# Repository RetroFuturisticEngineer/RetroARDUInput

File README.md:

# RetroARDUInput
Use USB Keyboards, Mice and Joysticks on PC/XT, PC/AT, Tandy 1000, Atari, Amiga, C64 and Apple

Requires Circuits@Home USB Host Shield 2.0 Library

Released before getting all components in a 100% working state, as I did not want to wait longer. Due to time limitations, I cannot guarantee to be finished soon with the last details, but by now, you can use all working components already. I will continue development but also encourage the retro computing community to help and contribute in fixing the last PS/2 and ADB issues.

You can find all required files here, the Arduino sketch (RetroArduInput_FW), the case, the PCB and a detailled documentation.

Current status of release:

Input:
- Working Input Devices:
  - Most normal USB Keyboards
  - Most normal USB Mice
  - Most USB Composite HIDs (Wireless USB Keyboard/Mouse)
  - USB Joysticks and Gamepads if they match to any of the implemented profiles
- Non-working or limited input devices (mostly limitations of the USB host shield library):
  - USB Hubs work random
  - No support for X-Box/Playstation USB gamepads
  - Problems with Gaming Keyboard/Mice with light effects etc.

Host Computers:
- Working computers to connect to:
  - PC/XT via Keyboard port
  - PC/AT via Keyboard port and PS/2 via adapter - includes typematic rate programming and LED set, however LEDs sometimes not properly set (only limitation)
  - Amiga 500 via Keyboard port when using an adapter to the internal keyboard port
  - Serial mouse with 2-button Microsoft and 3-button Logitech mode
  - Amiga/Atari mouse including switching of the X/Y pins between Atari and Amiga standard
  - Digital joystick, reacting to either joystick (normal joystick mode - uses a "dead zone" for analog joysticks to not immediately react on the slightest changes) and mouse (like a Commodore 1350 "Joymouse")
  - Analog joystick with 4 axis and 4 buttons
- Untested computers to connect to:
  - Tandy 1000 via keyboard port - adaptation of Adrian Black's PS/2 to Tandy, should work, but I cannot test it
  - Amiga 2000 via keyboard port - Should mostly work as mainly identical to Amiga 500, but uses a different routine during keyboard reset (Ctrl+Amiga+Amiga), which I cannot test du to not having an Amiga 2000 - Routine implemented but untested
  - Analog joystick when pulling the potentiometer to ground, which should enable to use it with BBC Micro, Tandy TRS-80, Tandy 1000 and Tano/Dragon with a proper adapter cable (attention, BBC Micro DB15 pinout different from PC!)
- Non-working or limited computers to connect to:
  - PS/2 via mouse port - detected by the BIOS and IRQ 12 properly reserved, works with a certain Logitech driver but not with Cutemouse or Windows
  - ADB for keyboard and mouse - Impleentation ongoing, switching on power via ADB works (currently mapped to Print Screen key), no keyboard scancodes implemented yet, mouse reporting started to implement but currently no reaction on my PowerMac to this

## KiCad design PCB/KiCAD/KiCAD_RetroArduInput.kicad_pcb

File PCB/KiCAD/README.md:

# General info

All KiCAD files if you want to modify the project for yourself, e.g., sparing out ports you do not need and so making the PCB smaller (but then, you also need to make a new case)

Gerber package for direct submission to PCB manufacturer in the Gerber folder

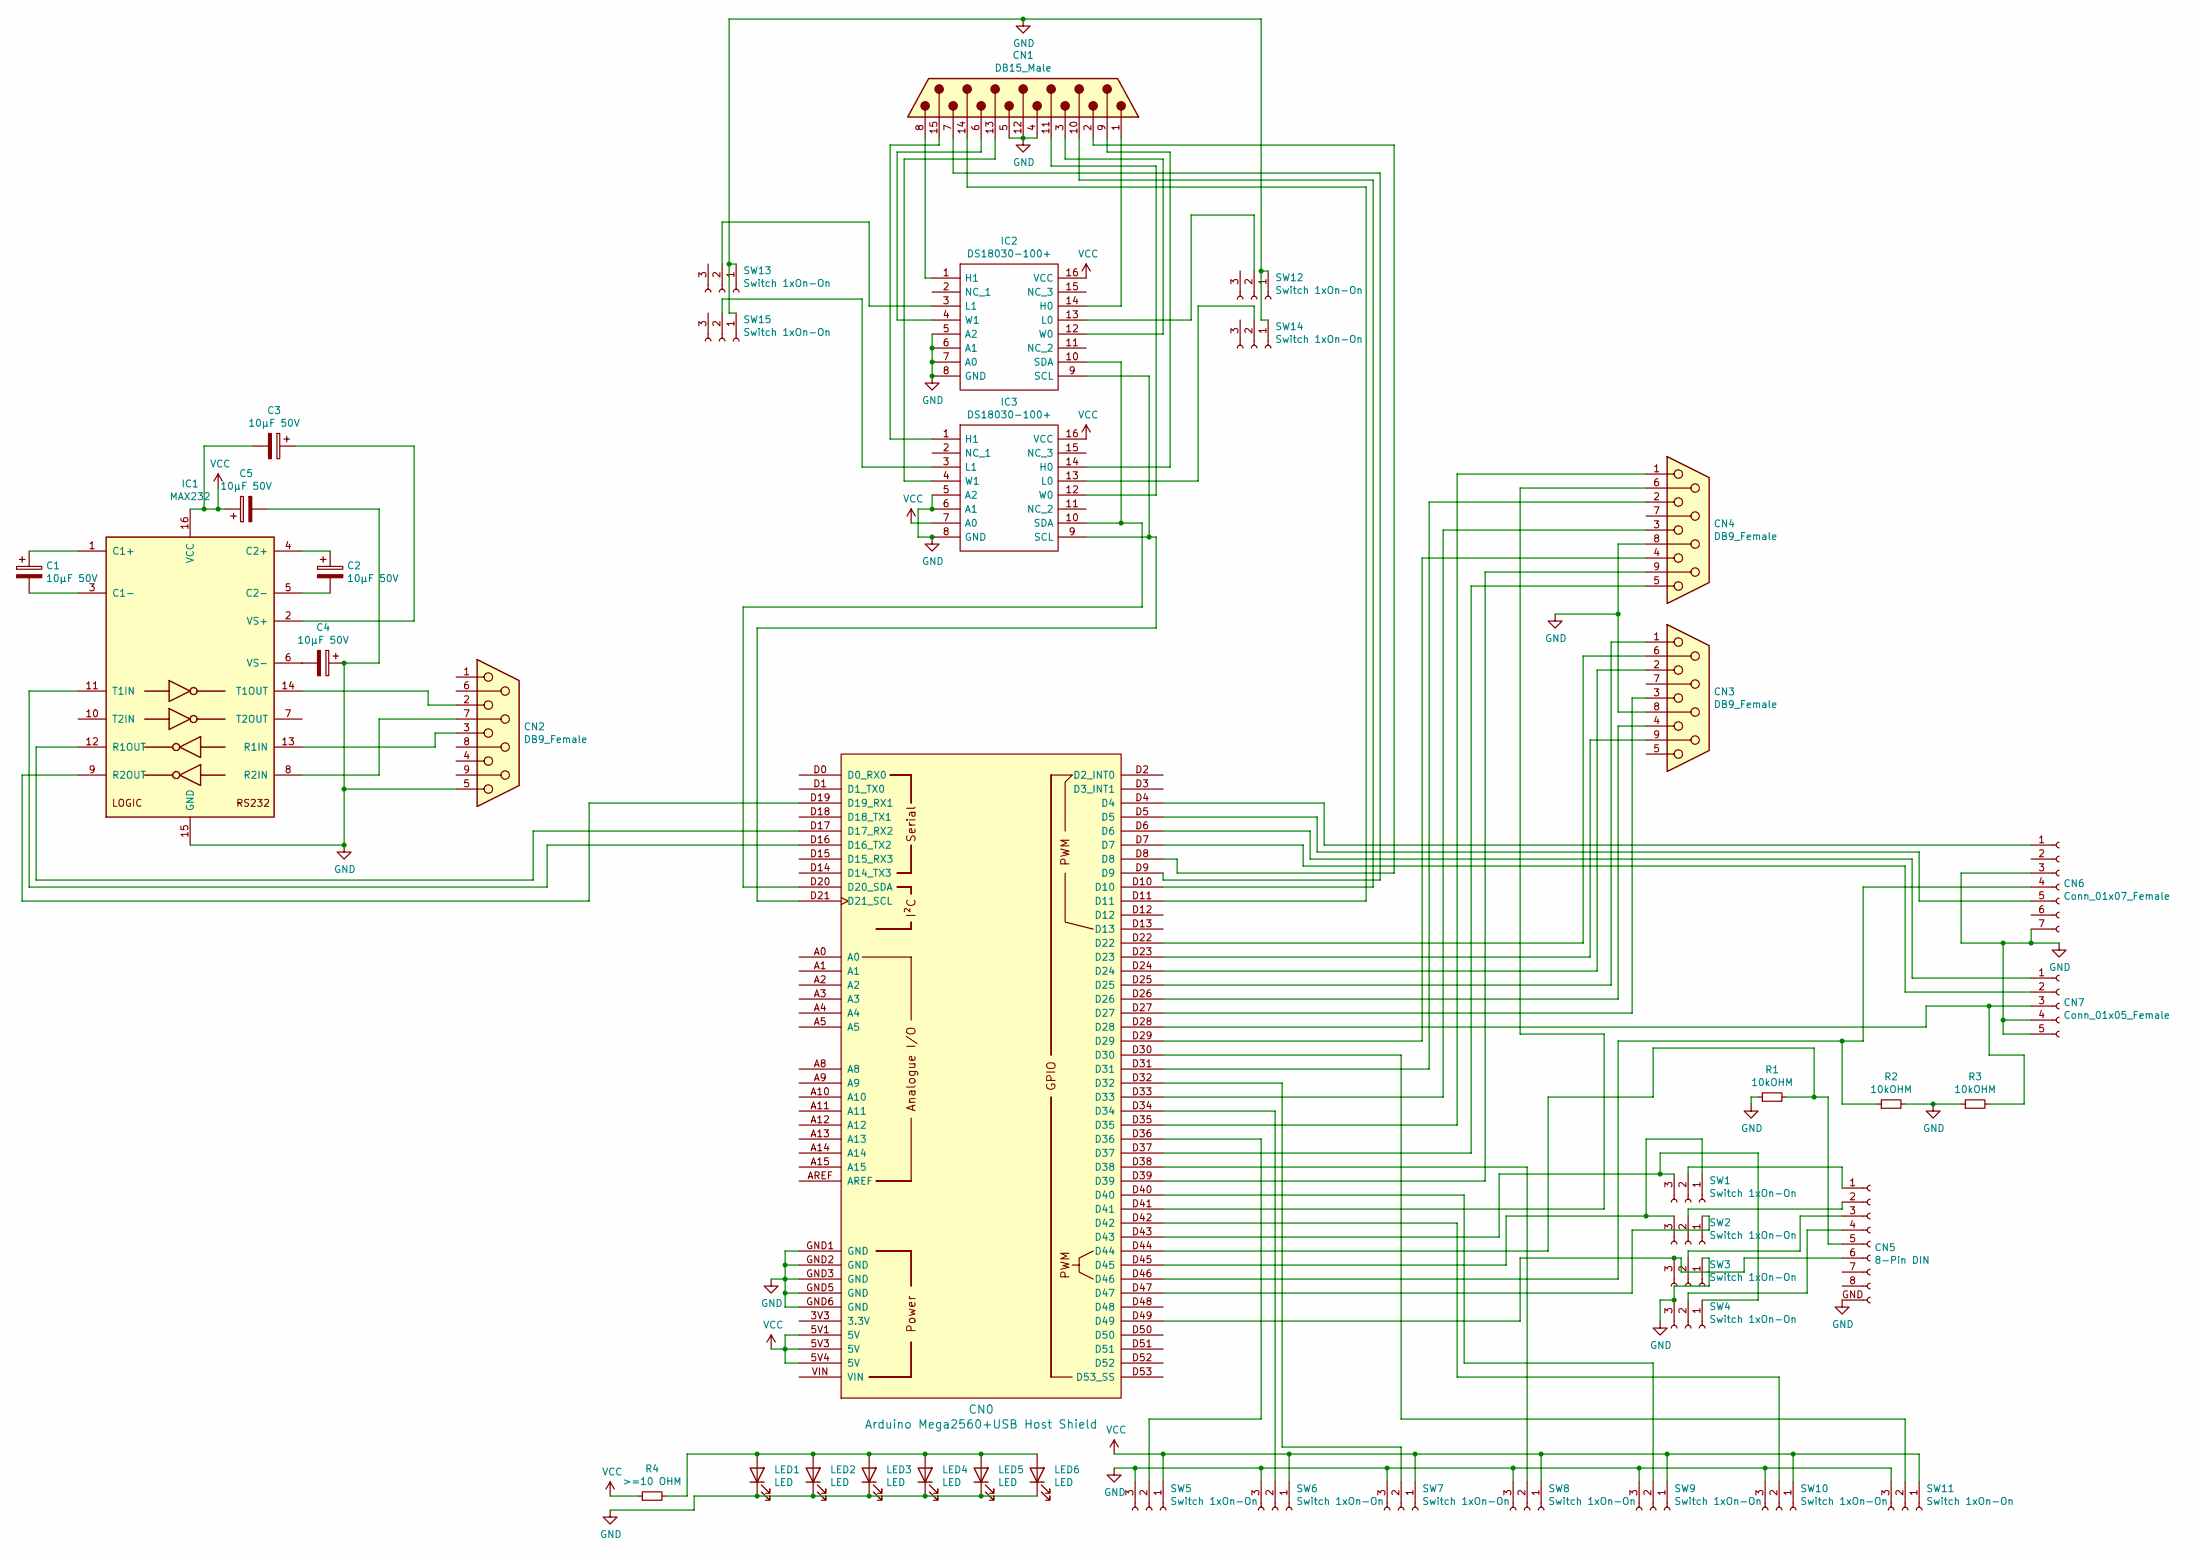
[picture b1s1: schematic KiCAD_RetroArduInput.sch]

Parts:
C1, C2, C3, C4, C5: 10μF 50V; CP_Radial_D5.0mm_P2.50mm
CN0: Arduino Mega2560+USB Host Shield; Arduino_Mega2560_Shield_Reduced
CN1: DB15_Male; DSUB-15_Male_Horizontal_P2.77x2.84mm_EdgePinOffset7.70mm_Ho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
CN2, CN3, CN4: DB9_Female; DSUB-9_Female_Horizontal_P2.77x2.84mm_EdgePinOffset9.90mm_H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
CN5: 8-Pin DIN; DIN8-270Print
CN6: Conn_01x07_Female; Connector_Mini-DIN_Female_6Pin_2rows
CN7: Conn_01x05_Female; Connector_Mini-DIN_Female_4Pin_2rows
IC1: MAX232; DIP-16_W7.62mm_Socket
IC2, IC3: DS18030-100+; DIP-16_W7.62mm_Socket; Manufacturer_Part_Number DS18030-010+; Mouser Part Number 700-DS18030-010
LED1, LED2, LED3, LED4, LED5, LED6: LED; LED_D5.0mm
R1, R2, R3: 10kOHM; R_Axial_DIN0309_L9.0mm_D3.2mm_P12.70mm_Horizontal
R4: >=10 OHM; R_Axial_DIN0309_L9.0mm_D3.2mm_P12.70mm_Horizontal
SW1, SW2, SW3, SW4, SW5, SW6, SW7, SW8, SW9, SW10, SW11, SW12, SW13, SW14, SW15: Switch 1xOn-On; CS12ANW03

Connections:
GND: C4.1, C5.2, CN0.GND1 (GND), CN0.GND2 (GND), CN0.GND3 (GND), CN0.GND5 (GND), CN0.GND6 (GND), CN1.4, CN1.5, CN1.12, CN2.5, CN3.8, CN4.8, CN5.GND, CN6.3, CN6.7, CN7.4, CN7.5, IC1.15 (GND), IC2.5 (A2), IC2.6 (A1), IC2.7 (A0), IC2.8 (GND), IC3.5 (A2), IC3.6 (A1), IC3.8 (GND), LED1.1 (K), LED2.1 (K), LED3.1 (K), LED4.1 (K), LED5.1 (K), LED6.1 (K), R1.1, R2.2, R3.1, SW3.1, SW4.3, SW5.3, SW6.3, SW7.3, SW8.3, SW9.3, SW10.3, SW11.3, SW12.1, SW13.1, SW14.1, SW15.1
unnamed: C1.1, IC1.1 (C1+)
unnamed: C1.2, IC1.3 (C1-)
unnamed: C2.1, IC1.4 (C2+)
unnamed: C2.2, IC1.5 (C2-)
unnamed: C3.1, IC1.2 (VS+)
unnamed: C4.2, IC1.6 (VS-)
unnamed: CN0.D4, CN6.1
unnamed: CN0.D5, CN6.5
unnamed: CN0.D6, CN7.1
unnamed: CN0.D7, CN7.2
unnamed: CN0.D8, CN1.2
unnamed: CN0.D9, CN1.7
unnamed: CN0.D10, CN1.10
unnamed: CN0.D11, CN1.14
unnamed: CN0.D16 (D16_TX2), IC1.11 (T1IN)
unnamed: CN0.D17 (D17_RX2), IC1.12 (R1OUT)
unnamed: CN0.D19 (D19_RX1), IC1.9 (R2OUT)
unnamed: CN0.D20 (D20_SDA), IC2.10 (SDA), IC3.10 (SDA)
unnamed: CN0.D21 (D21_SCL), IC2.9 (SCL), IC3.9 (SCL)
unnamed: CN0.D22, CN3.6
unnamed: CN0.D23, CN3.9
unnamed: CN0.D24, CN3.2
unnamed: CN0.D25, CN3.1
unnamed: CN0.D26, CN3.4
unnamed: CN0.D27, CN3.3
unnamed: CN0.D28, CN7.3, R3.2
unnamed: CN0.D29, CN4.4
unnamed: CN0.D30, SW11.2
unnamed: CN0.D31, CN4.2
unnamed: CN0.D32, SW7.2
unnamed: CN0.D33, CN4.3
unnamed: CN0.D34, SW6.2
unnamed: CN0.D35, CN4.1
unnamed: CN0.D36, SW5.2
unnamed: CN0.D37, CN4.5
unnamed: CN0.D38, SW8.2
unnamed: CN0.D39, CN4.9
unnamed: CN0.D40, SW9.2
unnamed: CN0.D41, CN4.6
unnamed: CN0.D42, SW10.2
unnamed: CN0.D43, SW1.3, SW4.1
unnamed: CN0.D44, CN5.5, R1.2
unnamed: CN0.D45, SW1.1, SW2.3
unnamed: CN0.D46, CN6.4, R2.1
unnamed: CN0.D47, SW2.1
unnamed: CN0.D49, CN5.6, SW3.3
unnamed: CN1.1, IC2.14 (H0)
unnamed: CN1.3, IC2.12 (W0)
unnamed: CN1.6, IC2.4 (W1)
unnamed: CN1.8, IC2.1 (H1)
unnamed: CN1.9, IC3.14 (H0)
unnamed: CN1.11 (P111), IC3.12 (W0)
unnamed: CN1.13, IC3.4 (W1)
unnamed: CN1.15, IC3.1 (H1)
unnamed: CN2.2, IC1.14 (T1OUT)
unnamed: CN2.3, IC1.13 (R1IN)
unnamed: CN2.7, IC1.8 (R2IN)
unnamed: CN5.1, SW1.2
unnamed: CN5.2, SW2.2
unnamed: CN5.3, SW3.2
unnamed: CN5.4, SW4.2
unnamed: IC2.3 (L1), SW13.2
unnamed: IC2.13 (L0), SW12.2
unnamed: IC3.3 (L1), SW15.2
unnamed: IC3.13 (L0), SW14.2
unnamed: LED1.2 (A), LED2.2 (A), LED3.2 (A), LED4.2 (A), LED5.2 (A), LED6.2 (A), R4.2
VCC: C3.2, C5.1, CN0.5V1 (5V), CN0.5V3 (5V), CN0.5V4 (5V), IC1.16 (VCC), IC2.16 (VCC), IC3.7 (A0), IC3.16 (VCC), R4.1, SW5.1, SW6.1, SW7.1, SW8.1, SW9.1, SW10.1, SW11.1

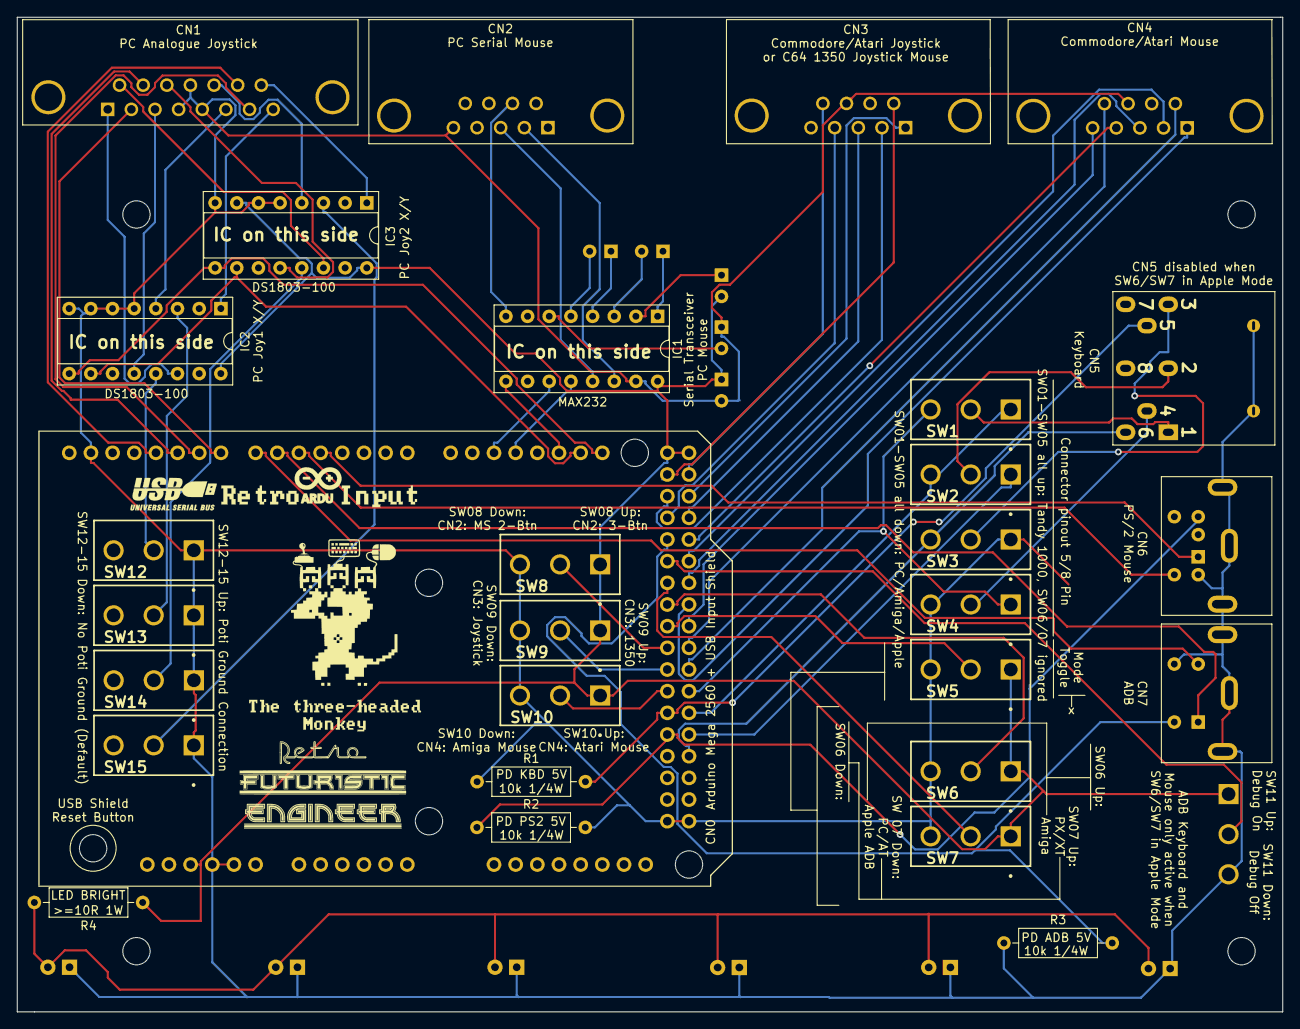
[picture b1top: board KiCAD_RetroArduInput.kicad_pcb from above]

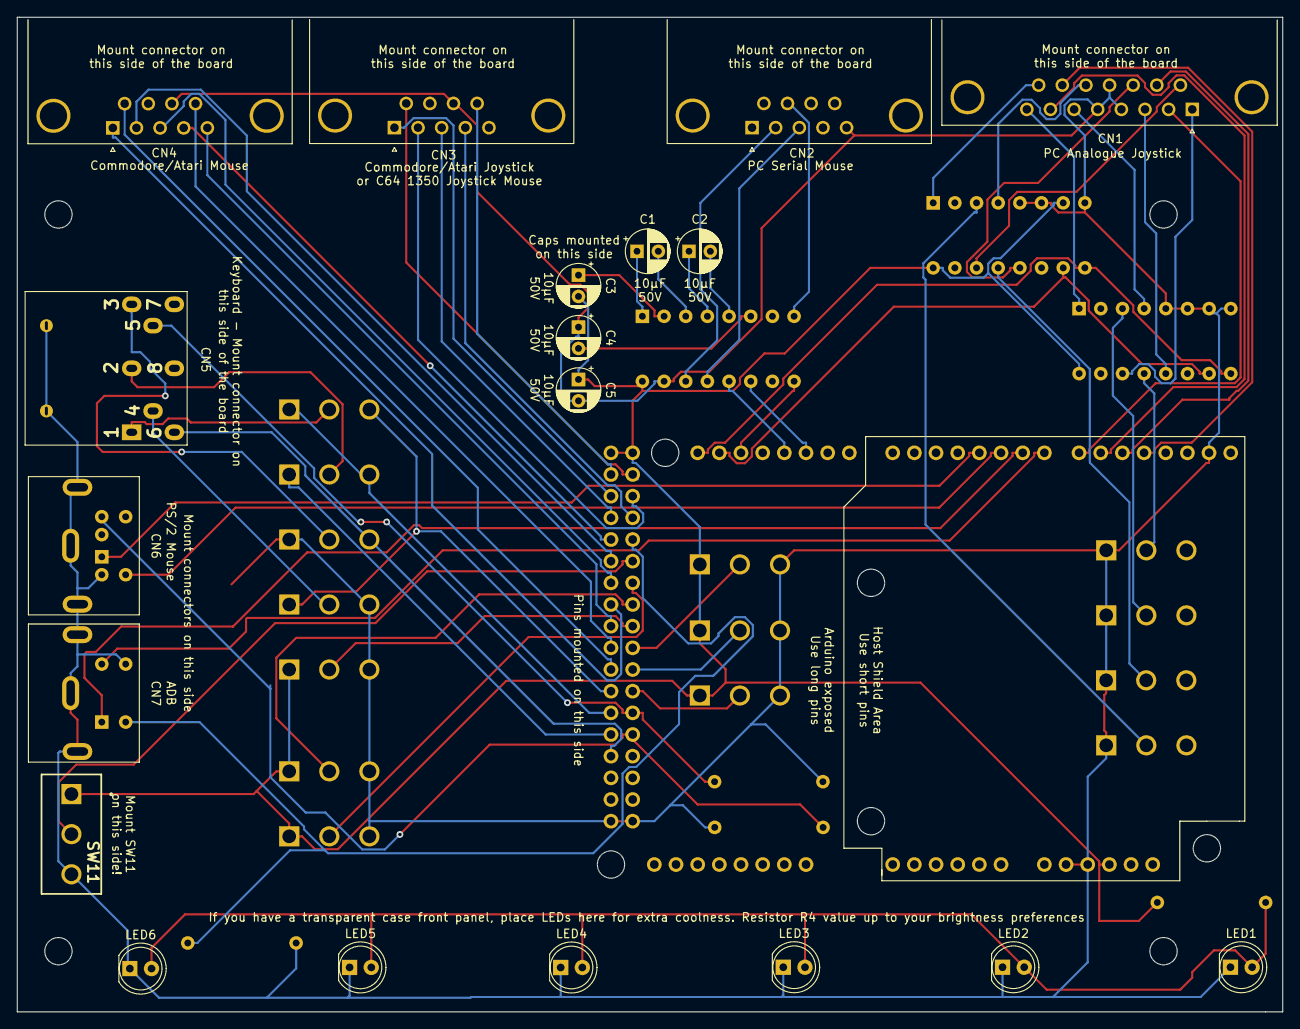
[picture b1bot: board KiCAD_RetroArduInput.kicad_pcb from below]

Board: 2 copper layers, 148.3 x 116.6 mm, 48 parts (19 on the bottom side), 68 nets.

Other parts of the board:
G_MONKEY: LOGO; Three-headed Monkey Logo
G_RFE: LOGO; RFE Logo
G_URAI: LOGO; RetroArduInput Logo
MH1, MH2, MH3, MH4: MountingHole_3.2mm_M3

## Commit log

2022-08-06 Create empty
